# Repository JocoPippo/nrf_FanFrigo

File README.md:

# Introduzione
In estate il frigo trivalente soffre molto a causa delle alte temperature che non consentono un scambio termico adeguato della serpentina di raffreddamente.
In commercio esistono soluzioni ma queste sono pienamente soddisfacenti.
Così ho deciso di realizzare una soluzione che permetesse di:
- regolare la velocità delle ventole in base alla temperature del vano;
- monitorare e controllare da remoto lo stato della board;
- la seconda ventola, sen non forzata da applicativo, viene attivata quando la prima supera la soglia del 70% di utilizzo così da ridurre la rumorosità;
- non pesare sui consumi elettrici quando non necessario.

La cartella "pheripheral_frigo" contiene il progetto per "Visual studio Code" del firmware della board di gestione delle ventole.
La cartella hardware contiene il progetto in Kicad 9 e i file gerber della scheda di controllo.
"AndroidApp" contiene l'applicativo Android di gestione della board.
Ci si riferisca al file README.md interno a ciascuna cartella per dettagli specifici.

# BOARD
Attualmente la revisione del pcb è la 2.0 in cui è stato aggiunto il supporto per il sensore tachimetrico per ciascuna ventola e la possibilità di valutare la tensione della batteria. Al fine di mantenere i consumi bassi si è scelto di inserire il partitore di tensione sotto il mosfet di controllo della ventola1. Questa scelta, benchè renda più semplice il pcb, complica la parte software che è ancora in fase di sviluppo. Probabilmente verrà sostituta aggiungendo un ulteriore switch.

# SOFTWARE GESTIONE
Basato sull'esempio "NRF Blinky" della nordic semiconductor è stato customizzato aggiungendo le funzionalità di riservatezza e di gestione della board.

La [pagina di gestione](AndroidApp/images/app1.png) consente di vedere lo stato corrente ed, eventualmente, di forzarlo. 

Nella [pagina di settings](AndroidApp/images/App2.png ) si può cambiare la password che avrà valore transitorio fino al nuovo reset della scheda o tramite il ciclo power-off -> power-on o attraverso la pressione del tasto di reset.

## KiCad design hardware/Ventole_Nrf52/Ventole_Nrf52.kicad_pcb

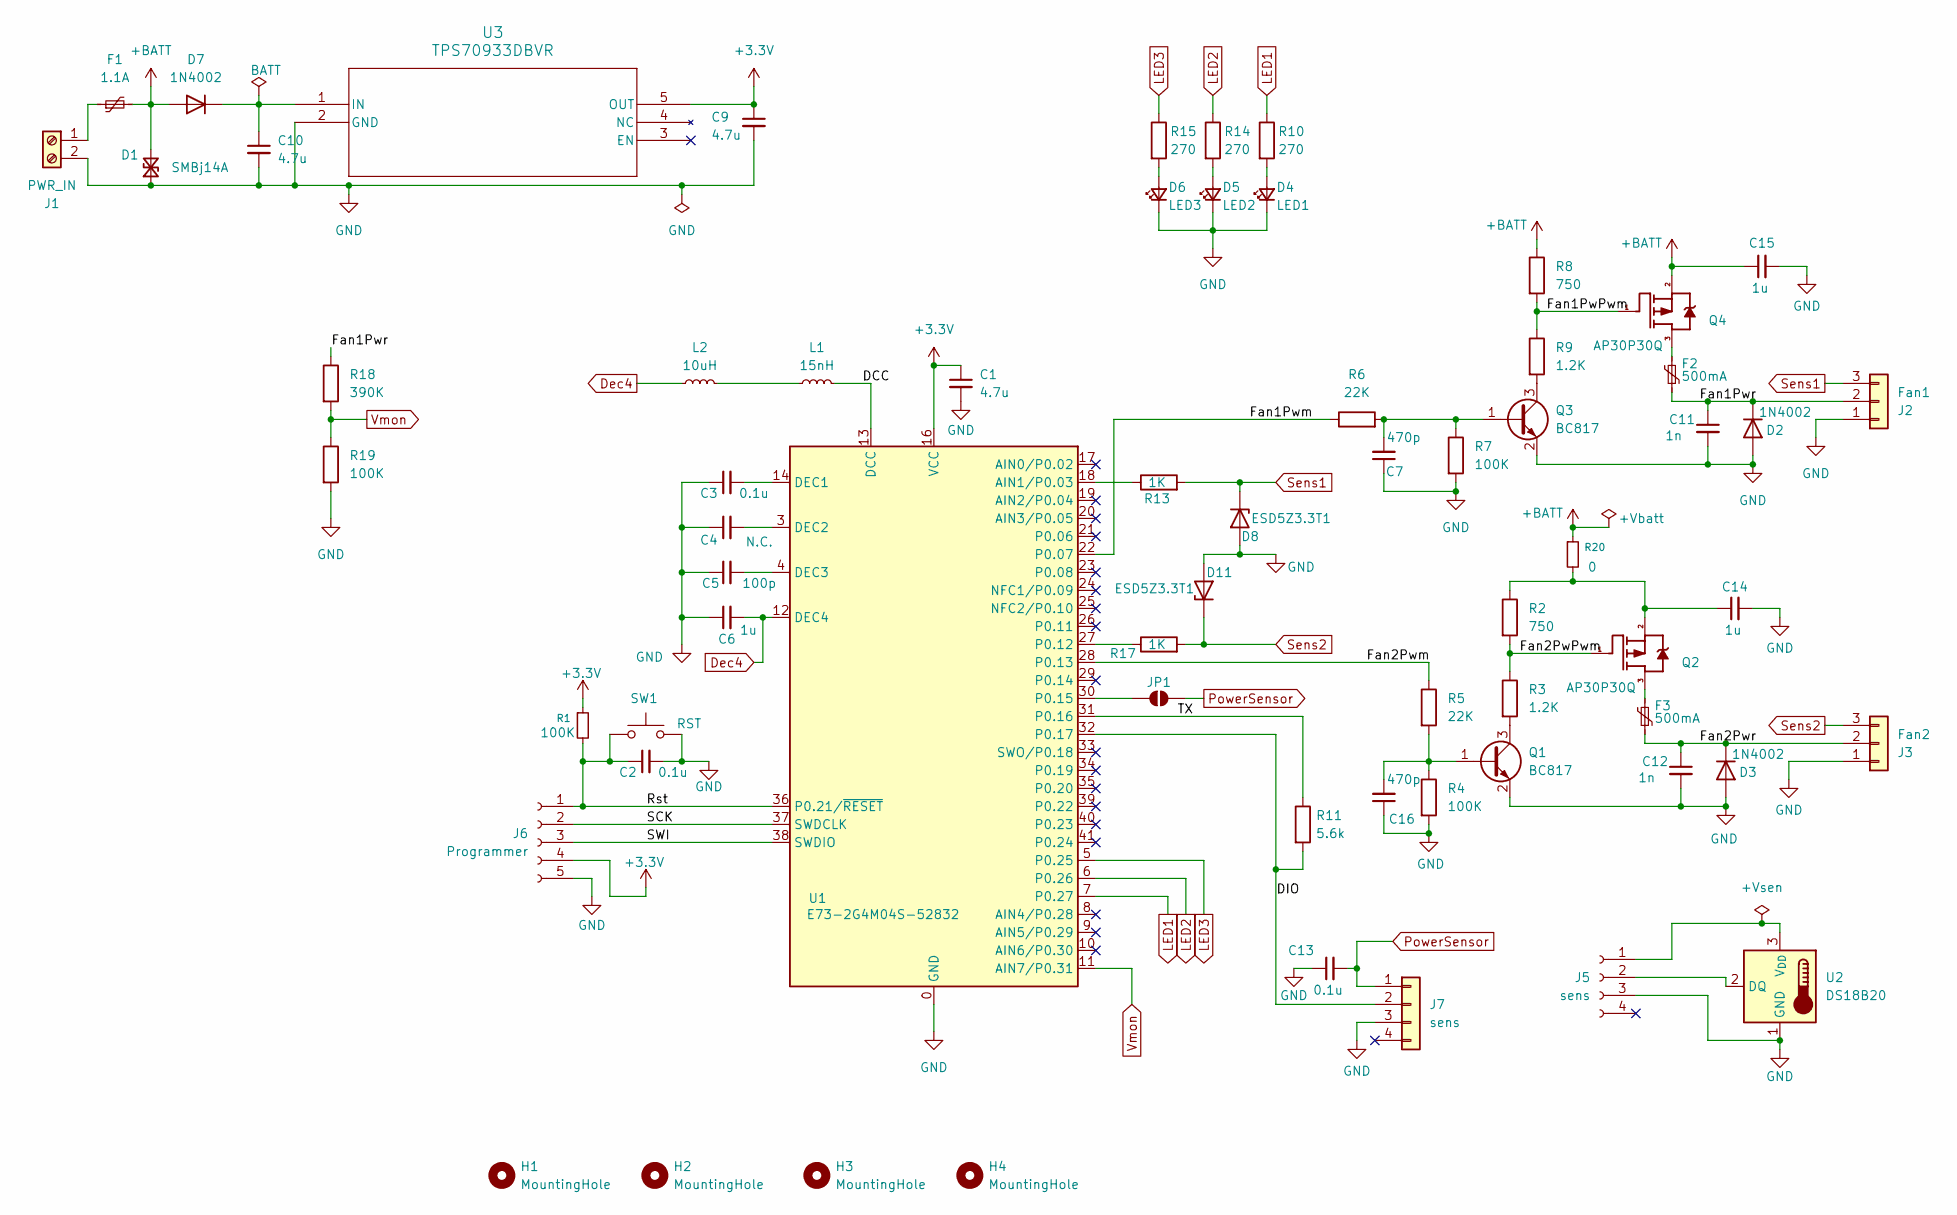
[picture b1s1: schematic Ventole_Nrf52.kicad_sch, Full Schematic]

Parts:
C1, C9, C10: 4.7u; C_0805_2012Metric_Pad1.18x1.45mm_HandSolder
C2, C3, C13: 0.1u; C_0805_2012Metric_Pad1.18x1.45mm_HandSolder
C4: N.C.; C_0805_2012Metric_Pad1.18x1.45mm_HandSolder
C5: 100p; C_0805_2012Metric_Pad1.18x1.45mm_HandSolder
C6: 1u; C_0805_2012Metric_Pad1.18x1.45mm_HandSolder
C7, C16: 470p; C_1206_3216Metric
C11, C12: 1n; C_0805_2012Metric_Pad1.18x1.45mm_HandSolder
C14, C15: 1u; C_1206_3216Metric
D1: SMBj14A; D_SMB
D2, D3, D7: 1N4002; D_SMA
D4: LED1; LED_0805_2012Metric_Pad1.15x1.40mm_HandSolder
D5: LED2; LED_0805_2012Metric_Pad1.15x1.40mm_HandSolder
D6: LED3; LED_0805_2012Metric_Pad1.15x1.40mm_HandSolder
D8, D11: ESD5Z3.3T1; D_SOD-523
F1: 1.1A; Fuse_1812_4532Metric_Pad1.30x3.40mm_HandSolder
F2, F3: 500mA; Fuse_1812_4532Metric_Pad1.30x3.40mm_HandSolder
H1, H2, H3, H4: MountingHole; MountingHole_2.2mm_M2
J1: PWR_IN; TerminalBlock_MX128-2-2.54_1x02_P2.54mm_Horizontal
J2: Fan1; JST_EH_B3B-EH-A_1x03_P2.50mm_Vertical
J3: Fan2; JST_EH_B3B-EH-A_1x03_P2.50mm_Vertical
J5: sens
J6: Programmer; Molex_PicoBlade_53048-0510_1x05_P1.25mm_Horizontal
J7: sens; PinSocket_1x04_P1.27mm_Vertical
JP1: PowerSensor; SolderJumper-2_P1.3mm_Open_RoundedPad1.0x1.5mm
L1: 15nH; L_0805_2012Metric_Pad1.05x1.20mm_HandSolder
L2: 10uH; L_0805_2012Metric_Pad1.05x1.20mm_HandSolder
Q1, Q3: BC817; SOT-23
Q2, Q4: AP30P30Q; DFN-8_3.0x3.0-E0.65_mos
R1, R4, R7, R19: 100K; R_0805_2012Metric_Pad1.20x1.40mm_HandSolder
R2, R8: 750; R_0805_2012Metric_Pad1.20x1.40mm_HandSolder
R3, R9: 1.2K; R_0805_2012Metric_Pad1.20x1.40mm_HandSolder
R5, R6: 22K; R_0805_2012Metric_Pad1.20x1.40mm_HandSolder
R10, R14, R15: 270; R_0805_2012Metric_Pad1.20x1.40mm_HandSolder
R11: 5.6k; R_0805_2012Metric_Pad1.20x1.40mm_HandSolder
R13, R17: 1K; R_0805_2012Metric_Pad1.20x1.40mm_HandSolder
R18: 390K; R_0805_2012Metric_Pad1.20x1.40mm_HandSolder
R20: 0; R_1206_3216Metric
SW1: RST; SW_SPST_B3U-1000P
U1: E73-2G4M04S-52832; E73-2G4M04S
U2: DS18B20; TO-92_Inline
U3: TPS70933DBVR; DBV5_TEX-M

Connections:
+3.3V: C1.1, C9.1, J6.4, R1.1, U1.16 (VCC), U3.5 (OUT)
+BATT: C15.1, D1.2 (A2), D7.2 (A), F1.2, Q4.2 (S), R8.1, R20.1
/DCC: L1.2, U1.13 (DCC)
/DIO: J7.2, R11.2, U1.32 (P0.17)
/Fan1PwPwm: Q4.1 (G), R8.2, R9.1
/Fan1Pwm: R6.1, U1.22 (P0.07)
/Fan1Pwr: C11.1, D2.1 (K), F2.1, J2.2, R18.1
/Fan2PwPwm: Q2.1 (G), R2.2, R3.1
/Fan2Pwm: R5.1, U1.28 (P0.13)
/Fan2Pwr: C12.1, D3.1 (K), F3.1, J3.2
/Rst: C2.1, J6.1, R1.2, SW1.1, U1.36 (P0.21/~RESET)
/SCK: J6.2, U1.37 (SWDCLK)
/SWI: J6.3, U1.38 (SWDIO)
/TX: R11.1, U1.31 (P0.16)
Dec4: C6.2, L2.1, U1.12 (DEC4)
GND: C1.2, C2.2, C3.1, C4.1, C5.1, C6.1, C7.1, C9.2, C10.2, C11.2, C12.2, C13.1, C14.2, C15.2, C16.1, D1.1 (A1), D2.2 (A), D3.2 (A), D4.1 (K), D5.1 (K), D6.1 (K), D8.2 (A), D11.2 (A), J1.2, J2.1, J3.1, J5.3, J6.5, J7.3, Q1.2 (E), Q3.2 (E), R4.2, R7.2, R19.2, SW1.2, U1.0 (GND), U1.1 (GND), U1.2 (GND), U1.15 (GND), U1.42 (GND), U1.43 (GND), U2.1 (GND), U3.2 (GND)
LED1: R10.1, U1.7 (P0.27)
LED2: R14.1, U1.6 (P0.26)
LED3: R15.1, U1.5 (P0.25)
unnamed: D4.2 (A), R10.2
unnamed: D5.2 (A), R14.2
unnamed: D6.2 (A), R15.2
unnamed: C10.1, D7.1 (K), U3.1 (IN)
unnamed: F1.1, J1.1
unnamed: J5.1, U2.3 (V_{DD})
unnamed: J5.2, U2.2 (DQ)
unnamed: JP1.1 (A), U1.30 (P0.15)
unnamed: L1.1, L2.2
unnamed: C16.2, Q1.1 (B), R4.1, R5.2
unnamed: Q1.3 (C), R3.2
unnamed: F3.2, Q2.3 (D)
unnamed: C14.1, Q2.2 (S), R2.1, R20.2
unnamed: C7.2, Q3.1 (B), R6.2, R7.1
unnamed: Q3.3 (C), R9.2
unnamed: F2.2, Q4.3 (D)
unnamed: R13.1, U1.18 (AIN1/P0.03)
unnamed: C3.2, U1.14 (DEC1)
unnamed: C4.2, U1.3 (DEC2)
unnamed: C5.2, U1.4 (DEC3)
unnamed: R17.1, U1.27 (P0.12)
PowerSensor: C13.2, J7.1, JP1.2 (B)
Sens1: D8.1 (K), J2.3, R13.2
Sens2: D11.1 (K), J3.3, R17.2
Vmon: R18.2, R19.1, U1.11 (AIN7/P0.31)

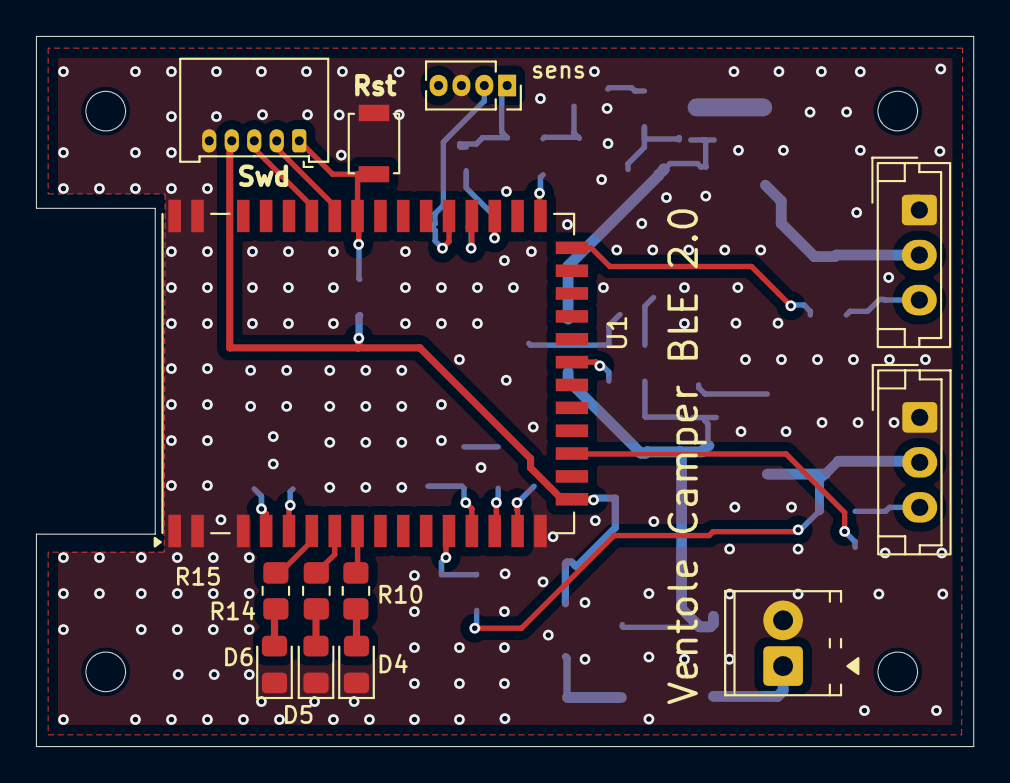
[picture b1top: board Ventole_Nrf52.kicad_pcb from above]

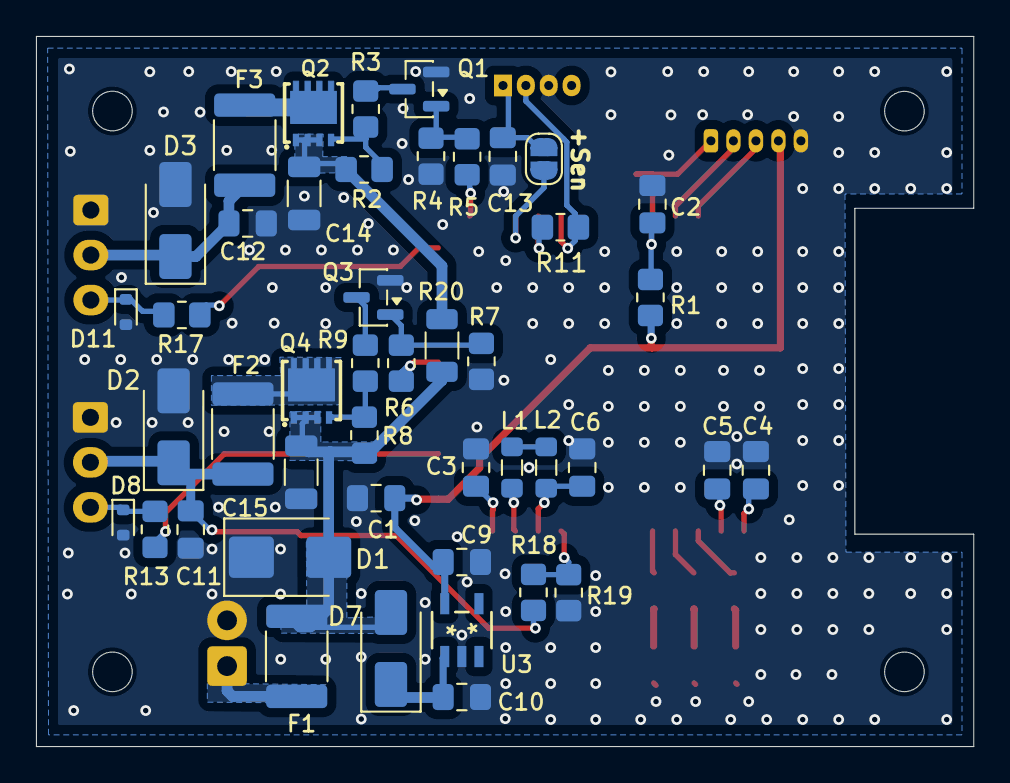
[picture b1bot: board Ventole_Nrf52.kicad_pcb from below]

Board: 2 copper layers, 52.1 x 39.5 mm, 62 parts (45 on the bottom side), 42 nets.

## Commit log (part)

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2026-06-21 Prima versione del progetto
    Progetto basato sul chip bluethooth nrf52832 della nordic semicondutor consente il controllo automatico della ventilazione del vano esterno del frigo trivalente del camper.
    Al fine di avere un efficienza migliore nel periodo estivo in cui le alte temperature ambientali non permettono il corretto scambio termico della serpentina.
2026-06-22 aggiornato readme
2026-06-22 aggiornato il readme di progetto
2026-06-22 Create toremove
2026-06-22 Libreria simboli kicad 9
2026-06-22 Aggiunta libreria footprint Kicad 9
2026-06-22 Aggiunto progetto Kicad 9
2026-06-22 Aggiunto parte applicazione android
2026-06-22 Aggiunta seconda parte Applicazione Android
2026-06-23 Create torem
    creazione cartella immagini pcb
2026-06-23 aggiunte immagini pcb
2026-06-23 aggiunte immagini applicazione
2026-06-23 aggiornamento readme
